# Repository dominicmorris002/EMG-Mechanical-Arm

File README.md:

# EMG Mechanical Arm

A myoelectric prosthetic arm that uses surface EMG signals to detect muscle gestures and drive a mechanical arm via a DC motor. The system consists of a **MyoWare 2.0 EMG sensor**, an **RP2040 microcontroller**, **DC motor driver H Bridge**, **Electrode Pads and Cable for Myoware Sensor**,  and a **DC motor** to control a 3D-printed mechanical arm.

---

## How It Works

The **RP2040** reads raw ADC values from the EMG sensor and uses the data to drive the H-Bridge to control the motor

---

## Repo Structure

```
EMG-Mechanical-Arm/
├── protomechanicalarm.py       # MicroPython code - Main product. Pre-tuned thresholds. Runs on RP2040 as main.py
├── learningarm.py              # MicroPython code - Optional. Adjusts thresholds automatically over time for better responsiveness
├── AITrainingCodeRP2040.py     # MicroPython code — runs on the RP2040 during AI data collection
├── AITrainingCodeComputer.py   # PC-side: collects data and trains the AI model
├── find_thresholds.py          # PC-side: finds ideal FLEX_ON / FLEX_OFF / FLEX_MAX thresholds
├── Doms PCB/                   # KiCad PCB design files
├── FinalPrint1/                # 3D print files (individual parts)
└── FULLPRINTFULLRightArm.3mf  # Full arm 3MF file for slicing
```

---

## Quickstart

You can choose to skip the AI thresholds and learning files as they work but are not needed for the product to run well. For the fastest and easiest approach plug in the PCB via USB to your computer.

1. **Download Thonny** and open `protomechanicalarm.py`
2. **Download MicroPython** onto the PCB through Thonny's interface at the bottom right — choose RP2040
3. **Save the file** by clicking File → Save As → MicroPython Device, and type `main.py`
4. The program will now always be stored on the chip and work as soon as plugged in

To change the trigger values of the sensor, simply change them in the code. The closer they are, the snappier they will be. Account for some amount of noise present. **14000 and 18000 are good starting numbers.**

---

## Optional: Learning Mode

If you want the arm to adapt and improve over time, use `learningarm.py` instead of `protomechanicalarm.py`. This version automatically adjusts the thresholds (`FLEX_ON`, `FLEX_OFF`, `FLEX_MAX`) based on your muscle signals during use. It learns from each flex/relax cycle and gets more responsive and personalized over time.

### How Learning Mode Works

- Tracks the peak muscle signal from each flex cycle
- Recalculates thresholds after each use based on a history of your last 10 peak signals
- Keeps thresholds within safe limits to prevent drift
- Prints threshold updates to the console so you can monitor adaptation

### When to Use Learning Mode

- You want the arm to automatically personalize to your muscle patterns
- You prefer not to manually tune threshold values
- You want the system to adapt to day-to-day variations in your signal

## Advanced: AI Training Mode

The AI training mode uses a Python script on your computer to collect muscle data and calculate optimal thresholds for you. This is optional and requires running Python scripts alongside the RP2040 code.

### Step 1 — Flash the RP2040 for Data Collection

Copy `AITrainingCodeRP2040.py` to your RP2040 as `main.py` using Thonny or `mpremote`. This streams raw ADC values over USB serial.

```python
# AITrainingCodeRP2040.py — runs on the RP2040
from machine import ADC, Pin
import time

adc = ADC(Pin(27))  # GP27 = ADC1

while True:
    val = adc.read_u16()  # 0–65535
    print(val)
    time.sleep_ms(1)      # ~1000 samples/sec
```

> **Important:** Close Thonny before running the PC training scripts. Both cannot hold the serial port at the same time.

---

### Step 2 — Install PC Dependencies

```bash
pip install numpy scipy pyserial tensorflow
```

---

### Step 3 — Collect EMG Data

```bash
python find_thresholds.py collect --label rest --port COM5 --seconds 20
python find_thresholds.py collect --label flex --port COM5 --seconds 20
```

Replace `COM5` with your actual serial port (`/dev/ttyACM0` on Linux/Mac).

---

### Step 4 — Process Windows

```bash
python find_thresholds.py windows
```

---

### Step 5 — Find Your Thresholds

```bash
python find_thresholds.py train_thresholds
```

This prints your personal `FLEX_ON`, `FLEX_OFF`, and `FLEX_MAX` values. Copy these into your motor control code on the RP2040.

---

## Bill of Materials (BOM)

> Costs omitted — use this as a copy-paste parts list for sourcing.

| Component | Description | Qty | Source / Part # |
|---|---|---|---|
| DC Motor | 12V High Torque Turbine Worm Geared Motor, 200 RPM, 8mm shaft | 1 | MECCANIXITY |
| Motor Driver | L298N Dual H-Bridge Motor Driver | 1 | Generic |
| EMG Sensor | MyoWare 2.0 compatible sensor cable | 1 | MyoWare |
| Electrode Pads | EMG Surface Electrodes, 6-pack | 3 packs | DigiKey #1528-2172-ND (Mfg #2773) |
| Microcontroller | RP2040 + PCB | 1 | Custom PCB via JLCPCB |
| Power Supply | 12V DC (5A) + 5V DC dual output power bank | 1 | ColdBye Dual Source Power Bank 12V and 5V |
| Enclosure | Custom 3D-printed enclosure | 1 | Print files in repo |
| Straps | Adjustable straps for arm attachment | 2 | Generic |
| Bearing (small) | 0.315" ID × 0.866" OD × 0.276" W | 15 | DigiKey #1995-1010-ND (Mfg #608-2RS-W/CHEVRONSRI2) |
| Bearing (large) | 0.591" ID × 1.26" OD × 0.354" W | 5 | DigiKey #1995-1014-ND (Mfg #6002ZZ) |
| Thread Inserts | 0.28" Dia × 0.38" H heat-set inserts | 50 | DigiKey #5519-HI-132-WH-ND (Mfg #HI-132-WH) |
| Machine Screws | Pan Phillips #10-32 | 50 | DigiKey #36-9909-ND (Mfg #9909) |
| Switches | SPST-NO 0.001A 5V detect switch | 50 | DigiKey #450-3349-ND (Mfg #JJOV0UL650NONPRBK) |
| PCBs | Custom arm PCBs assembled by JLCPCB | 1 | JLCPCB |
| Miscellaneous | Wires, breadboard, connectors | — | Generic |

---

## Hardware Notes

- EMG sensor connects to **GP27 (ADC1)** on the RP2040
- Motor driver IN1/IN2 pins connect to RP2040 GPIO outputs
- 12V powers the motor; RP2040 runs on 3.3V/5V USB — do not cross-connect
- Electrode placement: two signal electrodes along the muscle belly, one reference on a bony landmark (e.g., elbow)

---

## 3D Printing

The full arm model is included as `FULLPRINTFULLRightArm.3mf`. Individual parts are in the `FinalPrint1/` folder. Recommended print settings: H2D Printer Size with PLA Component.

---

## Project Gallery

<div align="center">

https://github.com/user-attachments/assets/b0d67ed7-32eb-4f09-bf58-b973187cbe4e

</div>

<div align="center">

</div>

<div align="center">

</div>

<div align="center">

</div>

<div align="center">

</div>

<div align="center">

</div>

---

## License

### Custom License — EMG Mechanical Arm

**Copyright © 2026 Dominic Morris** — All Rights Reserved (unless specified below)

This project is shared under a **modified open-source license** with the following terms:

#### Permitted Uses:
- **Personal & Educational Use:** You may freely use, study, modify, and build upon this work for personal, non-commercial, and educational purposes.
- **Open Source Contributions:** You may fork, modify, and improve this project for non-commercial use.

#### Requirements:
- **Attribution Required:** You must credit Dominic Morris and link to this repository in any public use, distribution, or derived work.
- **Share Modifications:** Any modifications, improvements, or derivative works must be publicly shared (open-sourced) and made available to the community with attribution.
- **No Commercial Resale Without Permission:** You may NOT sell, commercialize, or profit from this work or any derivative without explicit written permission and a commercial licensing agreement.

#### Commercial Use:
- If you wish to commercialize this work (sell it as a product, include it in a commercial offering, or generate profit):
  1. You **must obtain explicit written permission** from Dominic Morris
  2. Dominic Morris **must receive credit** as the original creator
  3. Dominic Morris **must receive a fair share of profit** (terms to be negotiated)
  4. A formal licensing agreement must be established before commercialization

#### Disclaimer:
THIS PROJECT IS PROVIDED "AS IS" WITHOUT WARRANTY OF ANY KIND, EXPRESS OR IMPLIED. THE AUTHOR IS NOT LIABLE FOR ANY DAMAGES, INJURIES, OR LOSSES RESULTING FROM USE OF THIS PROJECT.

---

**For inquiries regarding commercial licensing, collaborations, or permission requests, please contact Dominic Morris.**

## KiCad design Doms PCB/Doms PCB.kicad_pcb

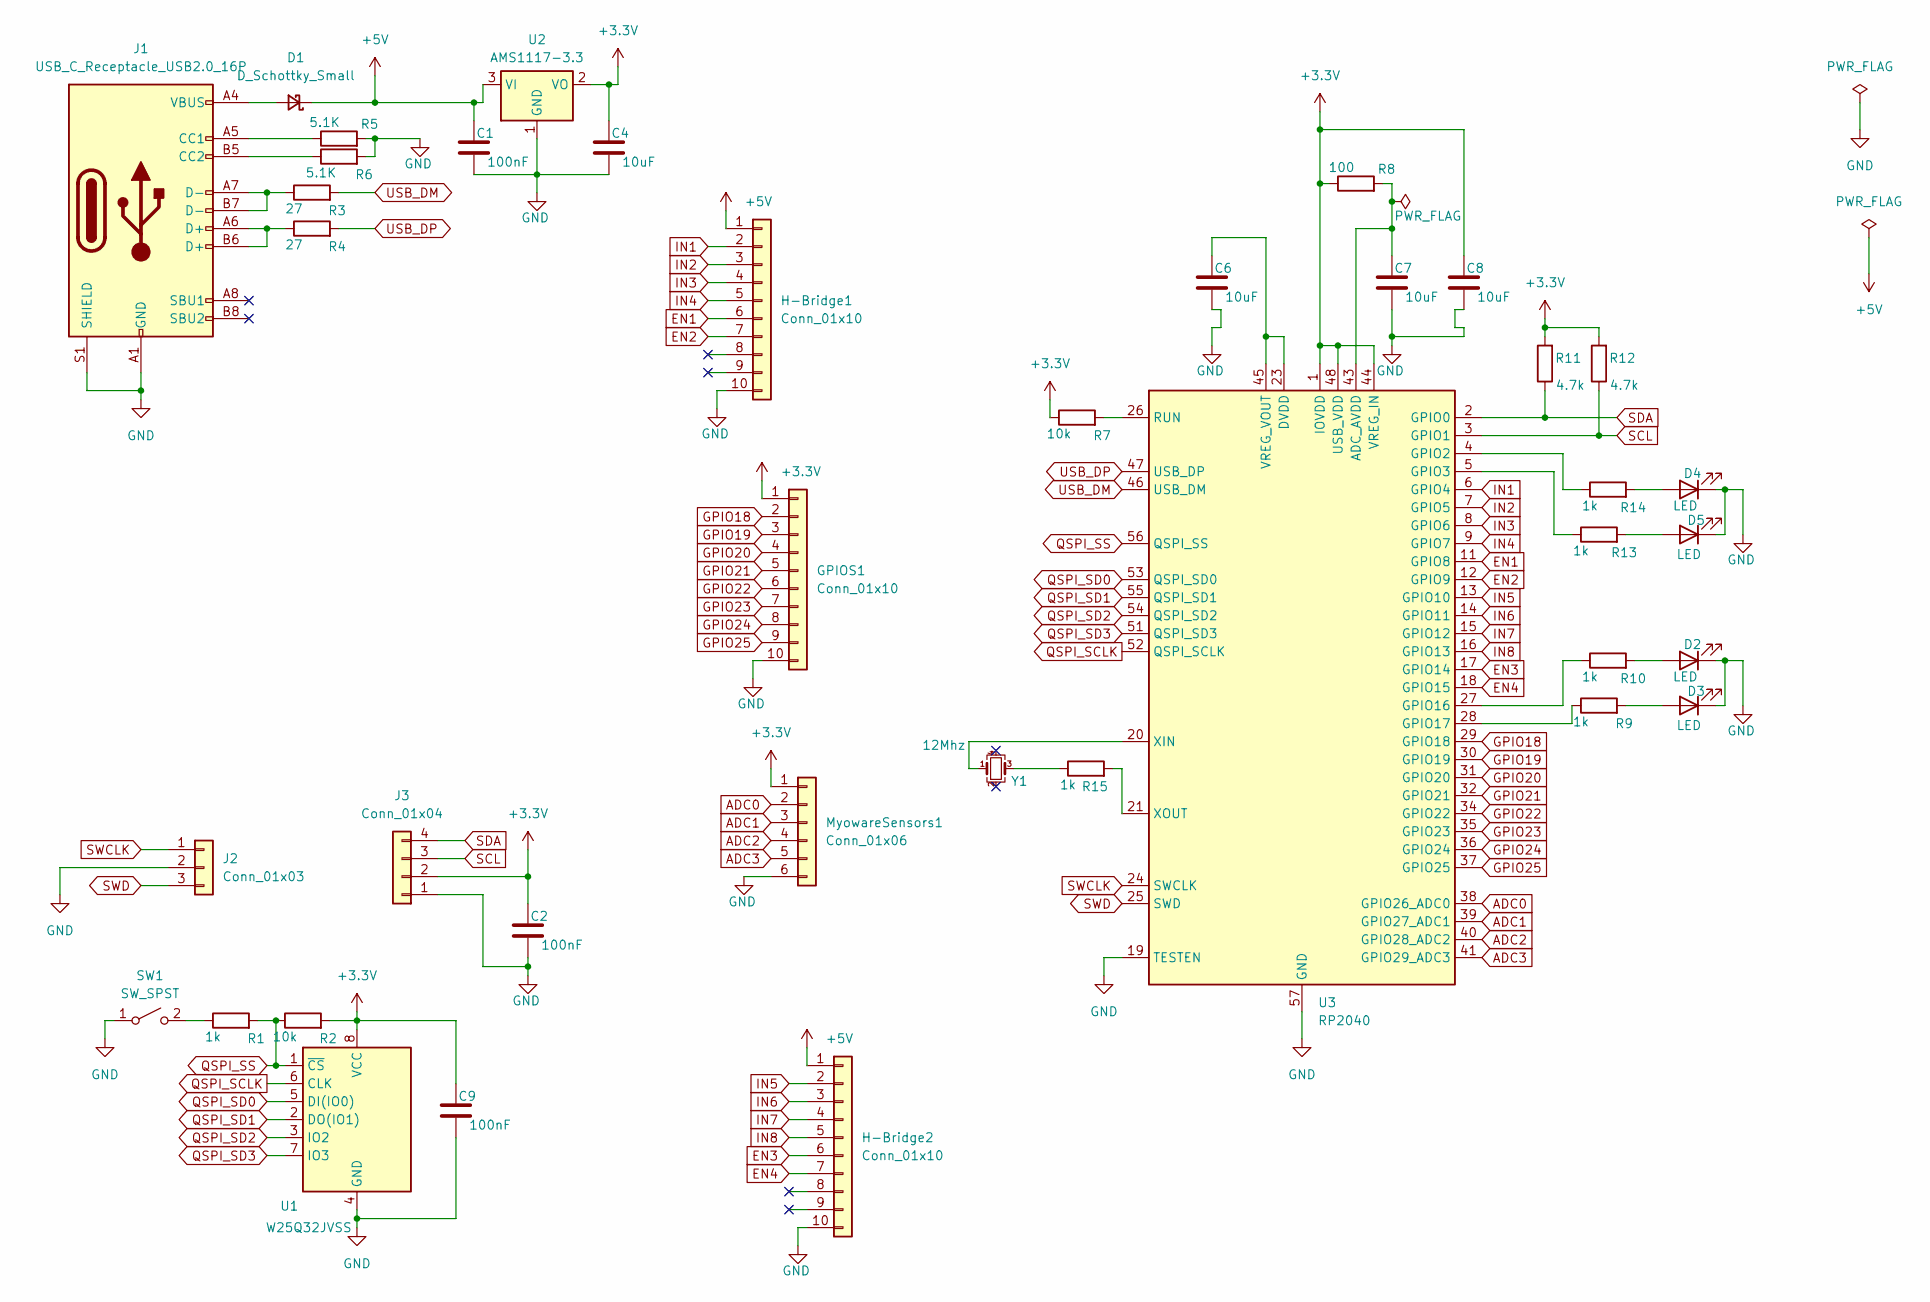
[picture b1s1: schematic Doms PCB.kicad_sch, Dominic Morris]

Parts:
C1, C2, C9: 100nF; C_0805_2012Metric
C4, C6, C7, C8: 10uF; C_0805_2012Metric
D1: D_Schottky_Small; D_SMA
D2, D3, D4, D5: LED; LED_0805_2012Metric
GPIOS1: Conn_01x10; PinHeader_1x10_P2.54mm_Vertical
H-Bridge1, H-Bridge2: Conn_01x10; PinHeader_1x10_P2.54mm_Vertical
J1: USB_C_Receptacle_USB2.0_16P; USB_C_Receptacle_HRO_TYPE-C-31-M-12
J2: Conn_01x03; PinSocket_1x03_P2.54mm_Vertical
J3: Conn_01x04; PinSocket_1x04_P2.54mm_Vertical
MyowareSensors1: Conn_01x06; PinHeader_1x06_P2.54mm_Vertical
R1, R9, R10, R13, R14, R15: 1k; R_0805_2012Metric
R2, R7: 10k; R_0805_2012Metric
R3, R4: 27; R_0805_2012Metric
R5, R6: 5.1K; R_0805_2012Metric
R8: 100; R_0805_2012Metric
R11, R12: 4.7k; R_0805_2012Metric
SW1: SW_SPST; SW_SPST_CK_RS282G05A3
U1: W25Q32JVSS; SOIC-8_5.23x5.23mm_P1.27mm
U2: AMS1117-3.3; SOT-223-3_TabPin2
U3: RP2040; QFN-56-1EP_7x7mm_P0.4mm_EP3.2x3.2mm
Y1: 12Mhz; Crystal_SMD_SeikoEpson_FA238V-4Pin_3.2x2.5mm

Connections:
+3.3V: C2.1, C4.1, C8.1, C9.1, GPIOS1.1, J3.2, MyowareSensors1.1, R2.2, R7.1, R8.1, R11.2, R12.2, U1.8 (VCC), U2.2 (VO), U3.1 (IOVDD), U3.10 (IOVDD), U3.22 (IOVDD), U3.33 (IOVDD), U3.42 (IOVDD), U3.44 (VREG_IN), U3.48 (USB_VDD), U3.49 (IOVDD)
+5V: C1.1, D1.1 (K), H-Bridge1.1, H-Bridge2.1, U2.3 (VI)
ADC0: MyowareSensors1.2, U3.38 (GPIO26_ADC0)
ADC1: MyowareSensors1.3, U3.39 (GPIO27_ADC1)
ADC2: MyowareSensors1.4, U3.40 (GPIO28_ADC2)
ADC3: MyowareSensors1.5, U3.41 (GPIO29_ADC3)
EN1: H-Bridge1.6, U3.11 (GPIO8)
EN2: H-Bridge1.7, U3.12 (GPIO9)
EN3: H-Bridge2.6, U3.17 (GPIO14)
EN4: H-Bridge2.7, U3.18 (GPIO15)
GND: C1.2, C2.2, C4.2, C6.2, C7.2, C8.2, C9.2, D2.1 (K), D3.1 (K), D4.1 (K), D5.1 (K), GPIOS1.10, H-Bridge1.10, H-Bridge2.10, J1.A1 (GND), J1.A12 (GND), J1.B1 (GND), J1.B12 (GND), J1.S1 (SHIELD), J2.2, J3.1, MyowareSensors1.6, R5.2, R6.2, SW1.1 (A), U1.4 (GND), U2.1 (GND), U3.19 (TESTEN), U3.57 (GND)
GPIO18: GPIOS1.2, U3.29 (GPIO18)
GPIO19: GPIOS1.3, U3.30 (GPIO19)
GPIO20: GPIOS1.4, U3.31 (GPIO20)
GPIO21: GPIOS1.5, U3.32 (GPIO21)
GPIO22: GPIOS1.6, U3.34 (GPIO22)
GPIO23: GPIOS1.7, U3.35 (GPIO23)
GPIO24: GPIOS1.8, U3.36 (GPIO24)
GPIO25: GPIOS1.9, U3.37 (GPIO25)
IN1: H-Bridge1.2, U3.6 (GPIO4)
IN2: H-Bridge1.3, U3.7 (GPIO5)
IN3: H-Bridge1.4, U3.8 (GPIO6)
IN4: H-Bridge1.5, U3.9 (GPIO7)
IN5: H-Bridge2.2, U3.13 (GPIO10)
IN6: H-Bridge2.3, U3.14 (GPIO11)
IN7: H-Bridge2.4, U3.15 (GPIO12)
IN8: H-Bridge2.5, U3.16 (GPIO13)
unnamed: D1.2 (A), J1.A4 (VBUS), J1.A9 (VBUS), J1.B4 (VBUS), J1.B9 (VBUS)
unnamed: D2.2 (A), R10.2
unnamed: D3.2 (A), R9.2
unnamed: D4.2 (A), R14.2
unnamed: D5.2 (A), R13.2
unnamed: J1.A5 (CC1), R5.1
unnamed: J1.B5 (CC2), R6.1
unnamed: J1.A6 (D+), J1.B6 (D+), R4.1
unnamed: J1.A7 (D-), J1.B7 (D-), R3.1
unnamed: R15.1, Y1.3
unnamed: R1.1, SW1.2 (B)
unnamed: C7.1, R8.2, U3.43 (ADC_AVDD)
unnamed: R14.1, U3.4 (GPIO2)
unnamed: R13.1, U3.5 (GPIO3)
unnamed: R10.1, U3.27 (GPIO16)
unnamed: R9.1, U3.28 (GPIO17)
unnamed: R7.2, U3.26 (RUN)
unnamed: C6.1, U3.23 (DVDD), U3.45 (VREG_VOUT), U3.50 (DVDD)
unnamed: U3.20 (XIN), Y1.1
unnamed: R15.2, U3.21 (XOUT)
QSPI_SCLK: U1.6 (CLK), U3.52 (QSPI_SCLK)
QSPI_SD0: U1.5 (DI(IO0)), U3.53 (QSPI_SD0)
QSPI_SD1: U1.2 (DO(IO1)), U3.55 (QSPI_SD1)
QSPI_SD2: U1.3 (IO2), U3.54 (QSPI_SD2)
QSPI_SD3: U1.7 (IO3), U3.51 (QSPI_SD3)
QSPI_SS: R1.2, R2.1, U1.1 (~CS), U3.56 (QSPI_SS)
SCL: J3.3, R12.1, U3.3 (GPIO1)
SDA: J3.4, R11.1, U3.2 (GPIO0)
SWCLK: J2.1, U3.24 (SWCLK)
SWD: J2.3, U3.25 (SWD)
USB_DM: R3.2, U3.46 (USB_DM)
USB_DP: R4.2, U3.47 (USB_DP)

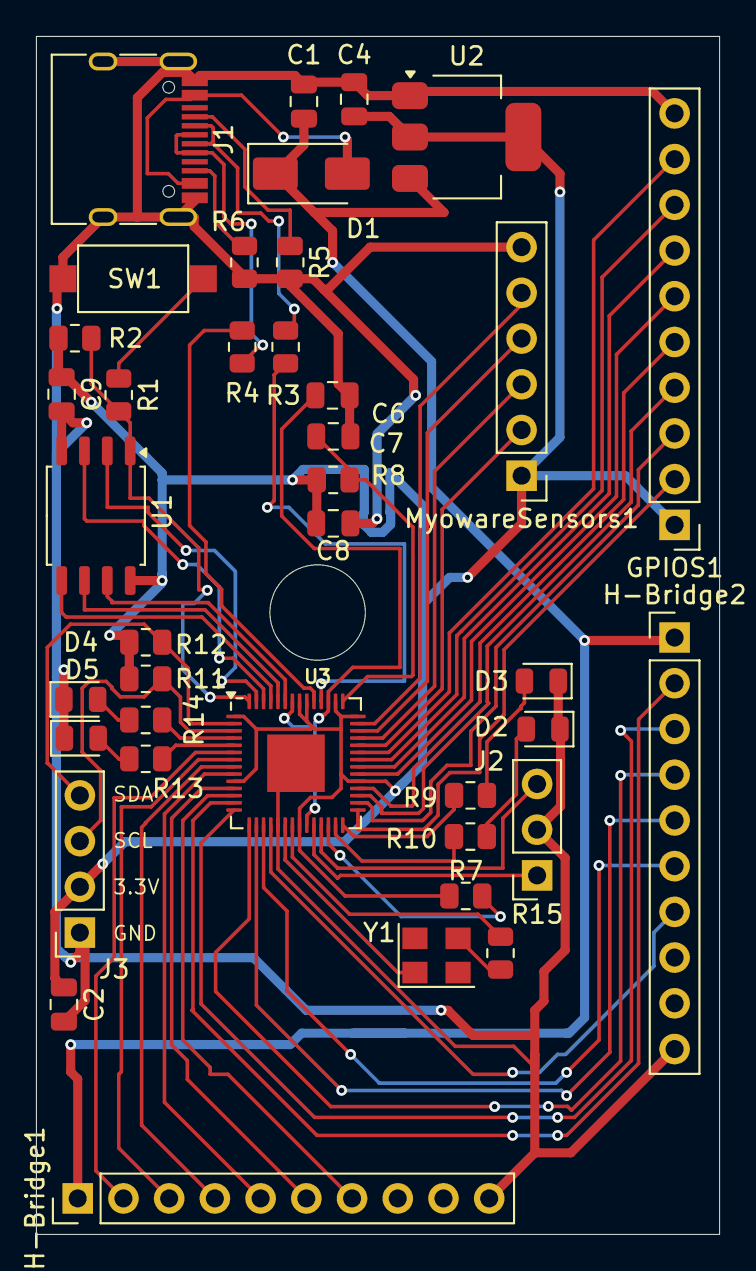
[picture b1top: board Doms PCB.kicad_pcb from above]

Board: 2 copper layers, 38.0 x 66.6 mm, 39 parts (0 on the bottom side), 59 nets.

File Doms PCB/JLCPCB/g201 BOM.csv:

"Reference","Value","Datasheet","Footprint","Qty","DNP"
"C1,C2,C9","100nF","","Capacitor_SMD:C_0805_2012Metric","3",""
"C3,C5","15pF","","Capacitor_SMD:C_0805_2012Metric","2",""
"C4,C6,C7,C8","10uF","","Capacitor_SMD:C_0805_2012Metric","4",""
"D1","D_Schottky_Small","","Diode_SMD:D_SMA","1",""
"D2,D3,D4,D5","LED","","LED_SMD:LED_0805_2012Metric","4",""
"GPIOS1,H-Bridge1,H-Bridge2","Conn_01x10","","Connector_PinHeader_2.54mm:PinHeader_1x10_P2.54mm_Vertical","3",""
"J1","USB_C_Receptacle_USB2.0_16P","https://www.usb.org/sites/default/files/documents/usb_type-c.zip","Connector_USB:USB_C_Receptacle_HRO_TYPE-C-31-M-12","1",""
"J2","Conn_01x03","","Connector_PinSocket_2.54mm:PinSocket_1x03_P2.54mm_Vertical","1",""
"J3","Conn_01x04","","Connector_PinSocket_2.54mm:PinSocket_1x04_P2.54mm_Vertical","1",""
"MyowareSensors1","Conn_01x06","","Connector_PinHeader_2.54mm:PinHeader_1x06_P2.54mm_Vertical","1",""
"R1,R9,R10,R13,R14,R15","1k","","Resistor_SMD:R_0805_2012Metric","6",""
"R2,R7","10k","","Resistor_SMD:R_0805_2012Metric","2",""
"R3,R4","27","","Resistor_SMD:R_0805_2012Metric","2",""
"R5,R6","5.1K","","Resistor_SMD:R_0805_2012Metric","2",""
"R8","100","","Resistor_SMD:R_0805_2012Metric","1",""
"R11,R12","4.7k","","Resistor_SMD:R_0805_2012Metric","2",""
"R16","50","","Resistor_SMD:R_0805_2012Metric","1",""
"SW1","SW_SPST","","Button_Switch_SMD:SW_SPST_CK_RS282G05A3","1",""
"U1","W25Q32JVSS","http://www.winbond.com/resource-files/w25q32jv%20revg%200327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","Package_SO:SOIC-8_5.23x5.23mm_P1.27mm","1",""
"U2","AMS1117-3.3","http://www.advanced-monolithic.com/pdf/ds1117.pdf","Package_TO_SOT_SMD:SOT-223-3_TabPin2","1",""
"U3","RP2040","https://datasheets.raspberrypi.com/rp2040/rp2040-datasheet.pdf","Package_DFN_QFN:QFN-56-1EP_7x7mm_P0.4mm_EP3.2x3.2mm","1",""
"Y1","12Mhz","","Crystal:Crystal_SMD_SeikoEpson_FA238V-4Pin_3.2x2.5mm","1",""

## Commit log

2026-05-05 Create LICENSE
2026-05-05 Update LICENSE
2026-05-18 Improve image sizing and add comprehensive custom license protecting work from commercial misuse
2026-05-18 Revise print settings in README
    Updated recommended print settings for the full arm model.
2026-05-18 Change demo video link in README
    Updated the demo video link in the project gallery.
2026-05-18 Add Learning Mode section with learningarm.py code and keep original Quickstart text exactly
